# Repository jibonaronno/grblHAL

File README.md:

# grblHAL
STM32F401 GRBL Controller over BlackPill board.

Schematic and layout are completed. Screw Terminal Connectors and optos are aligned. Added 4 TMC2208.<br>

### Inspired from <a href="https://github.com/avizienis/Minimal-Black-Pill--STM32F4xx-BOB-for-grblHAL">Minimal-Black-Pill--STM32F4xx-BOB-for-grblHAL</a><br>
<br>

### Our Kicad design below.<br/>
<br>
<br>
<br>

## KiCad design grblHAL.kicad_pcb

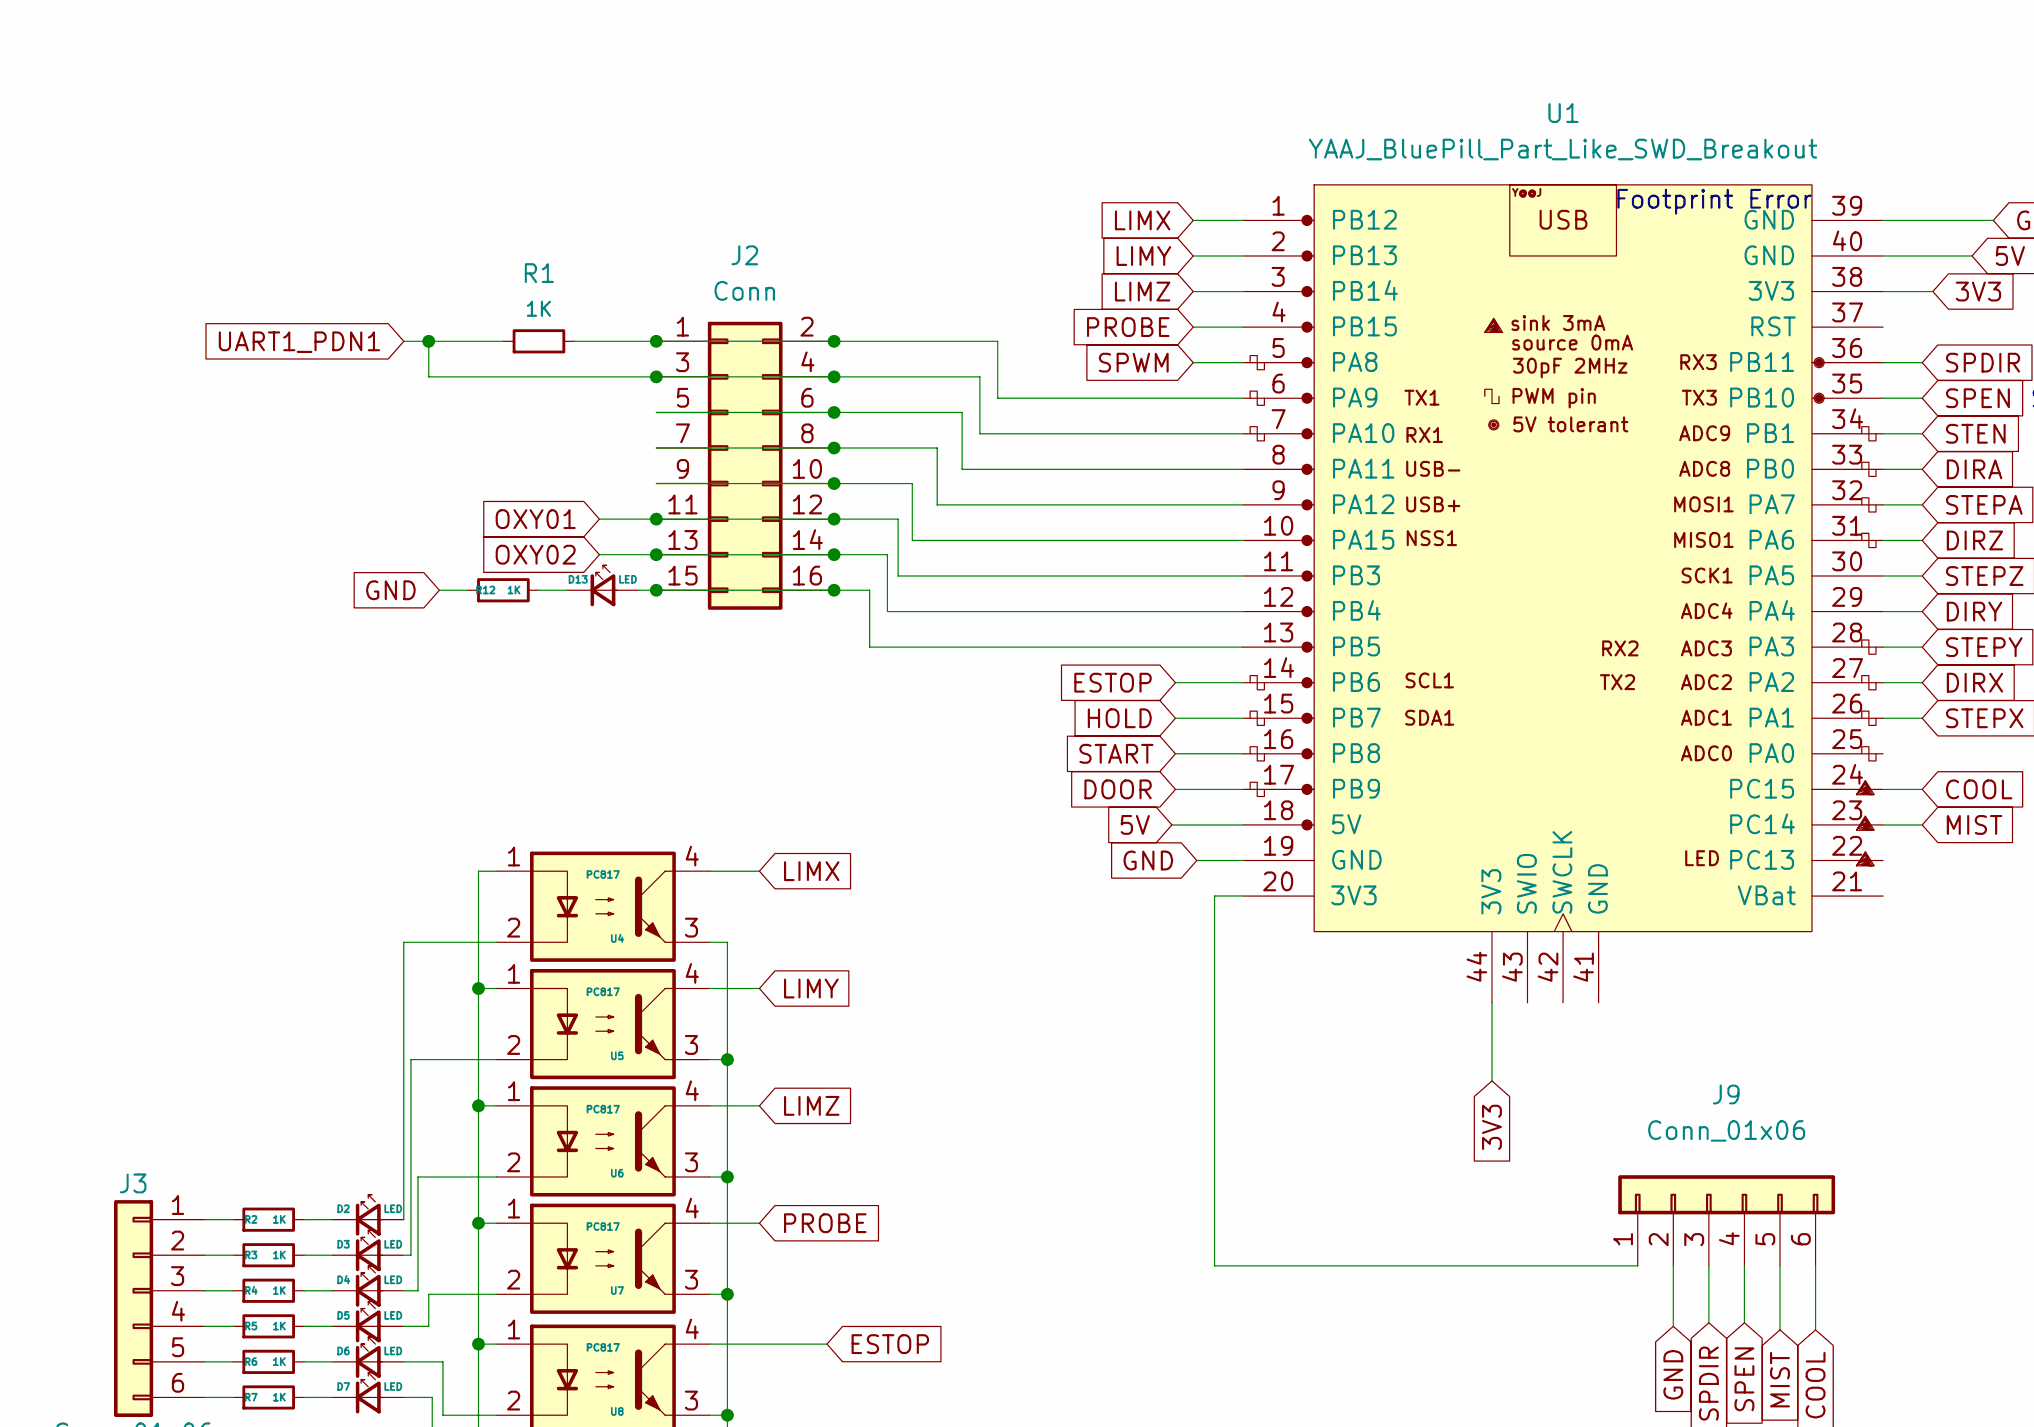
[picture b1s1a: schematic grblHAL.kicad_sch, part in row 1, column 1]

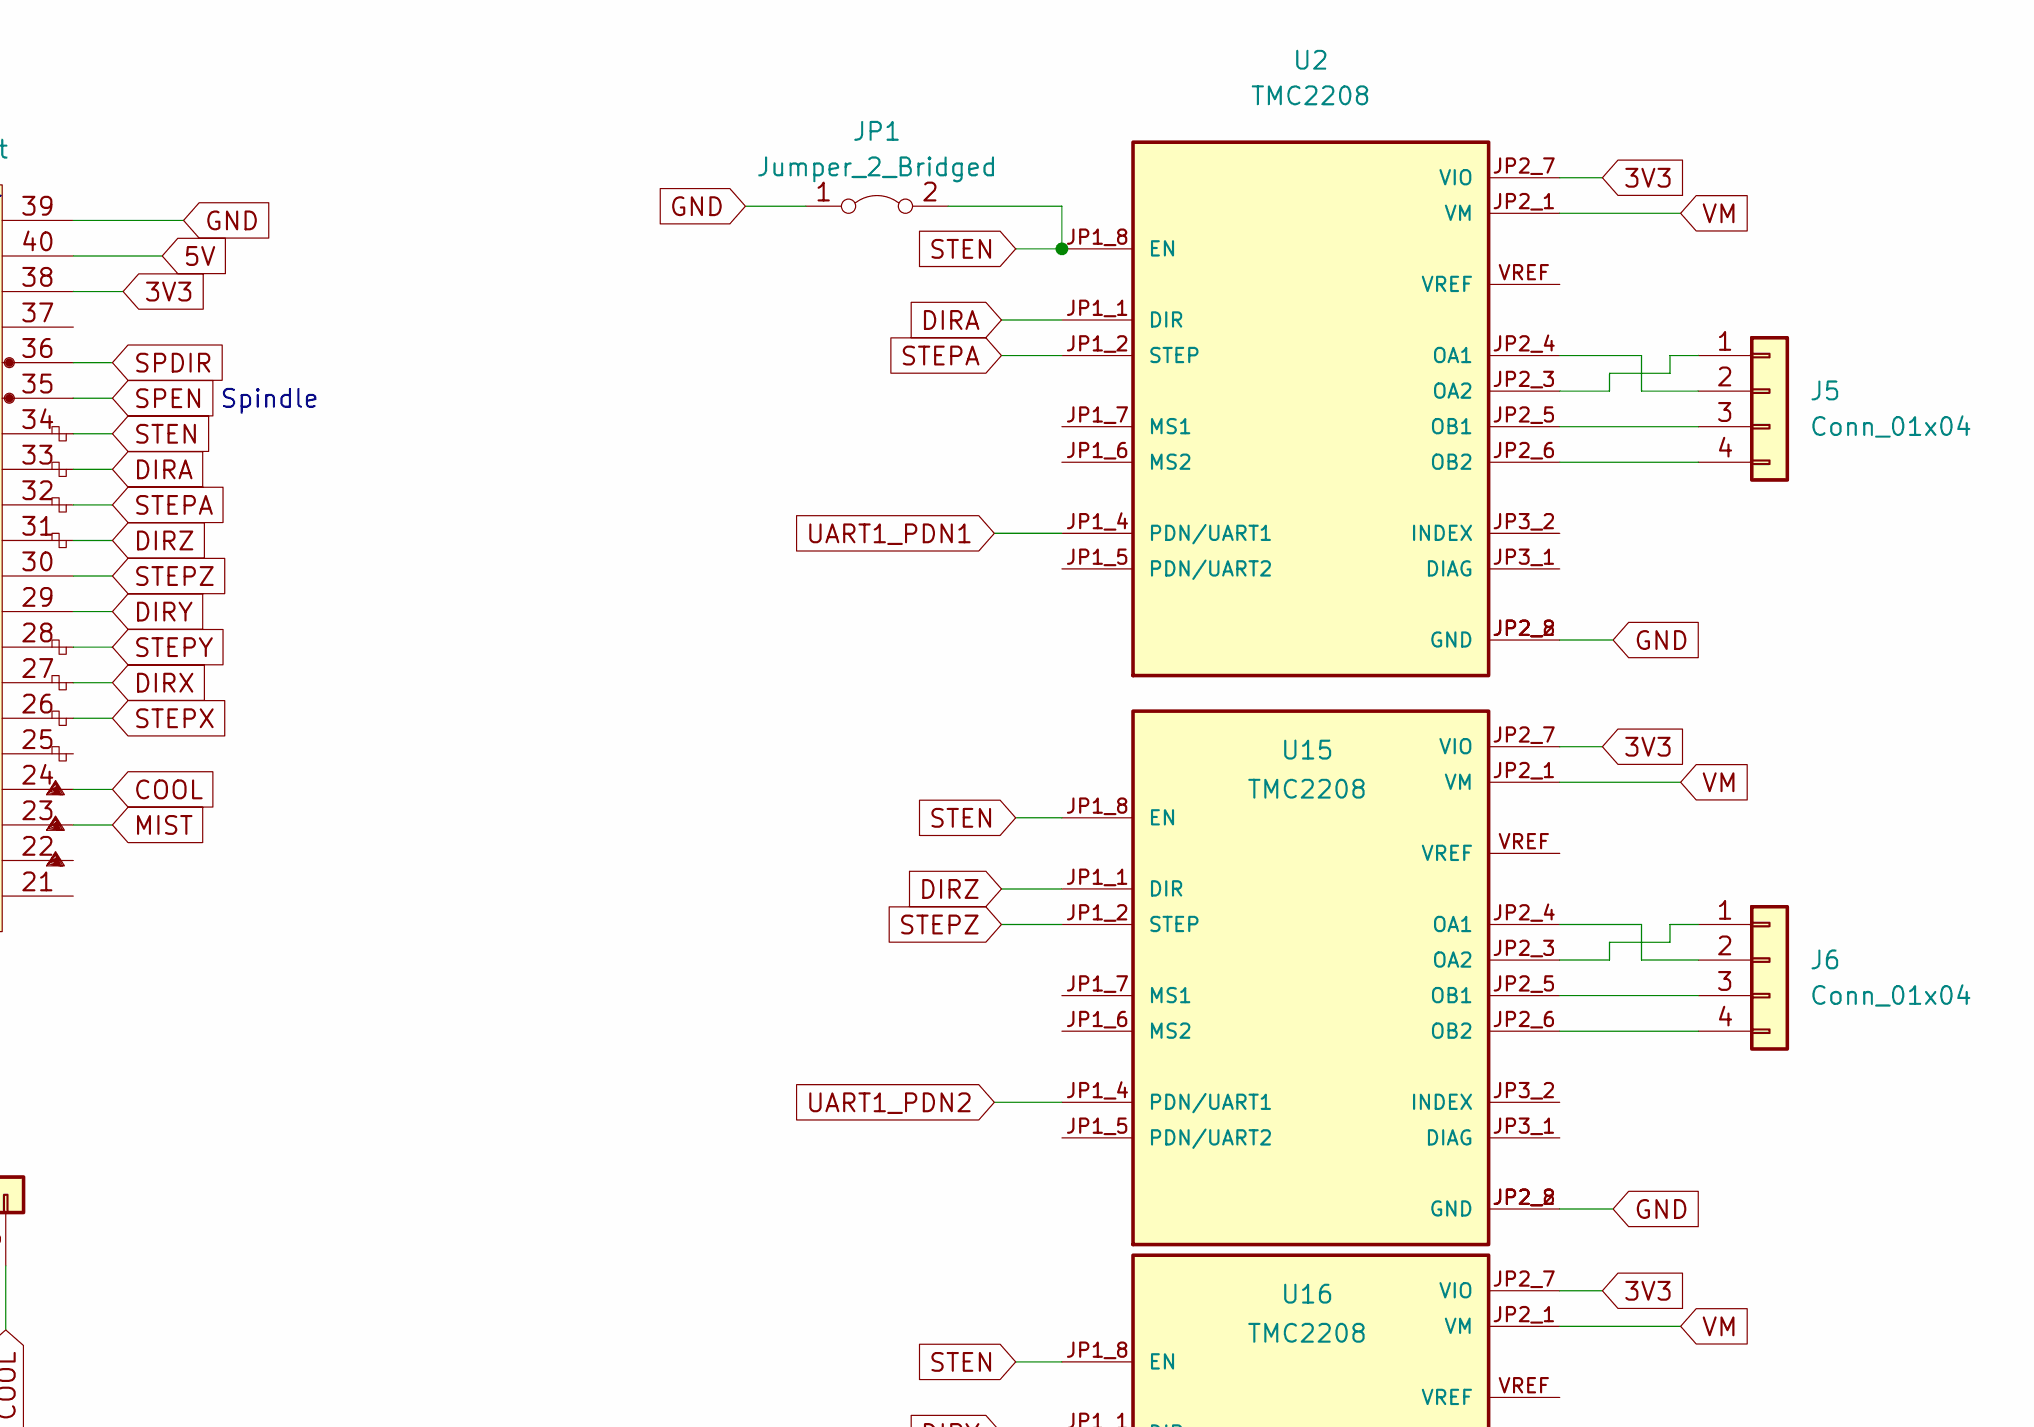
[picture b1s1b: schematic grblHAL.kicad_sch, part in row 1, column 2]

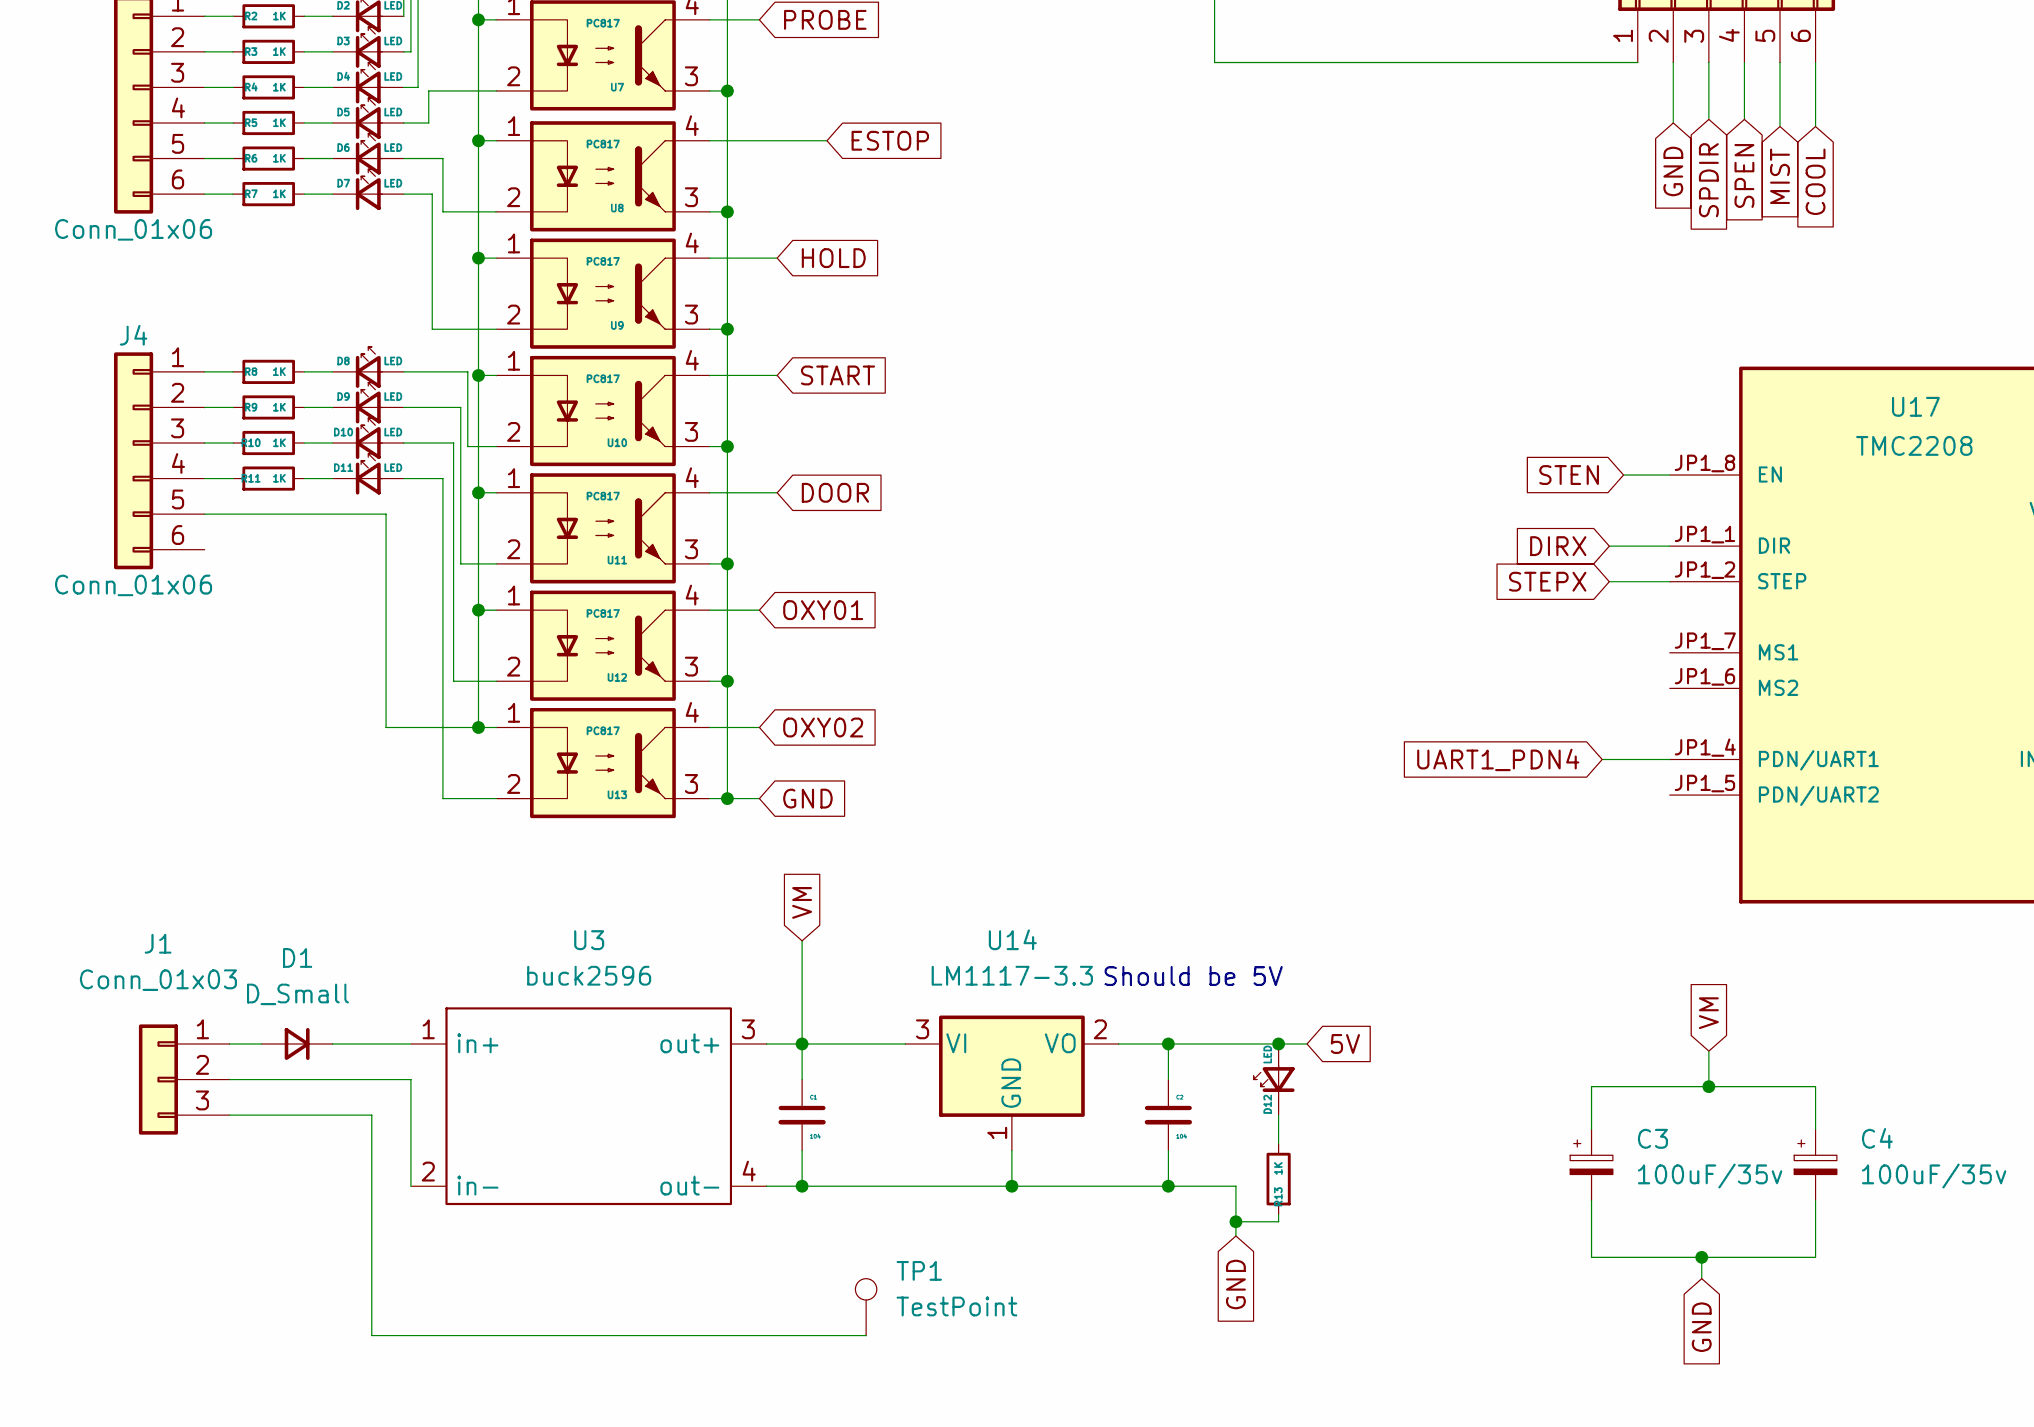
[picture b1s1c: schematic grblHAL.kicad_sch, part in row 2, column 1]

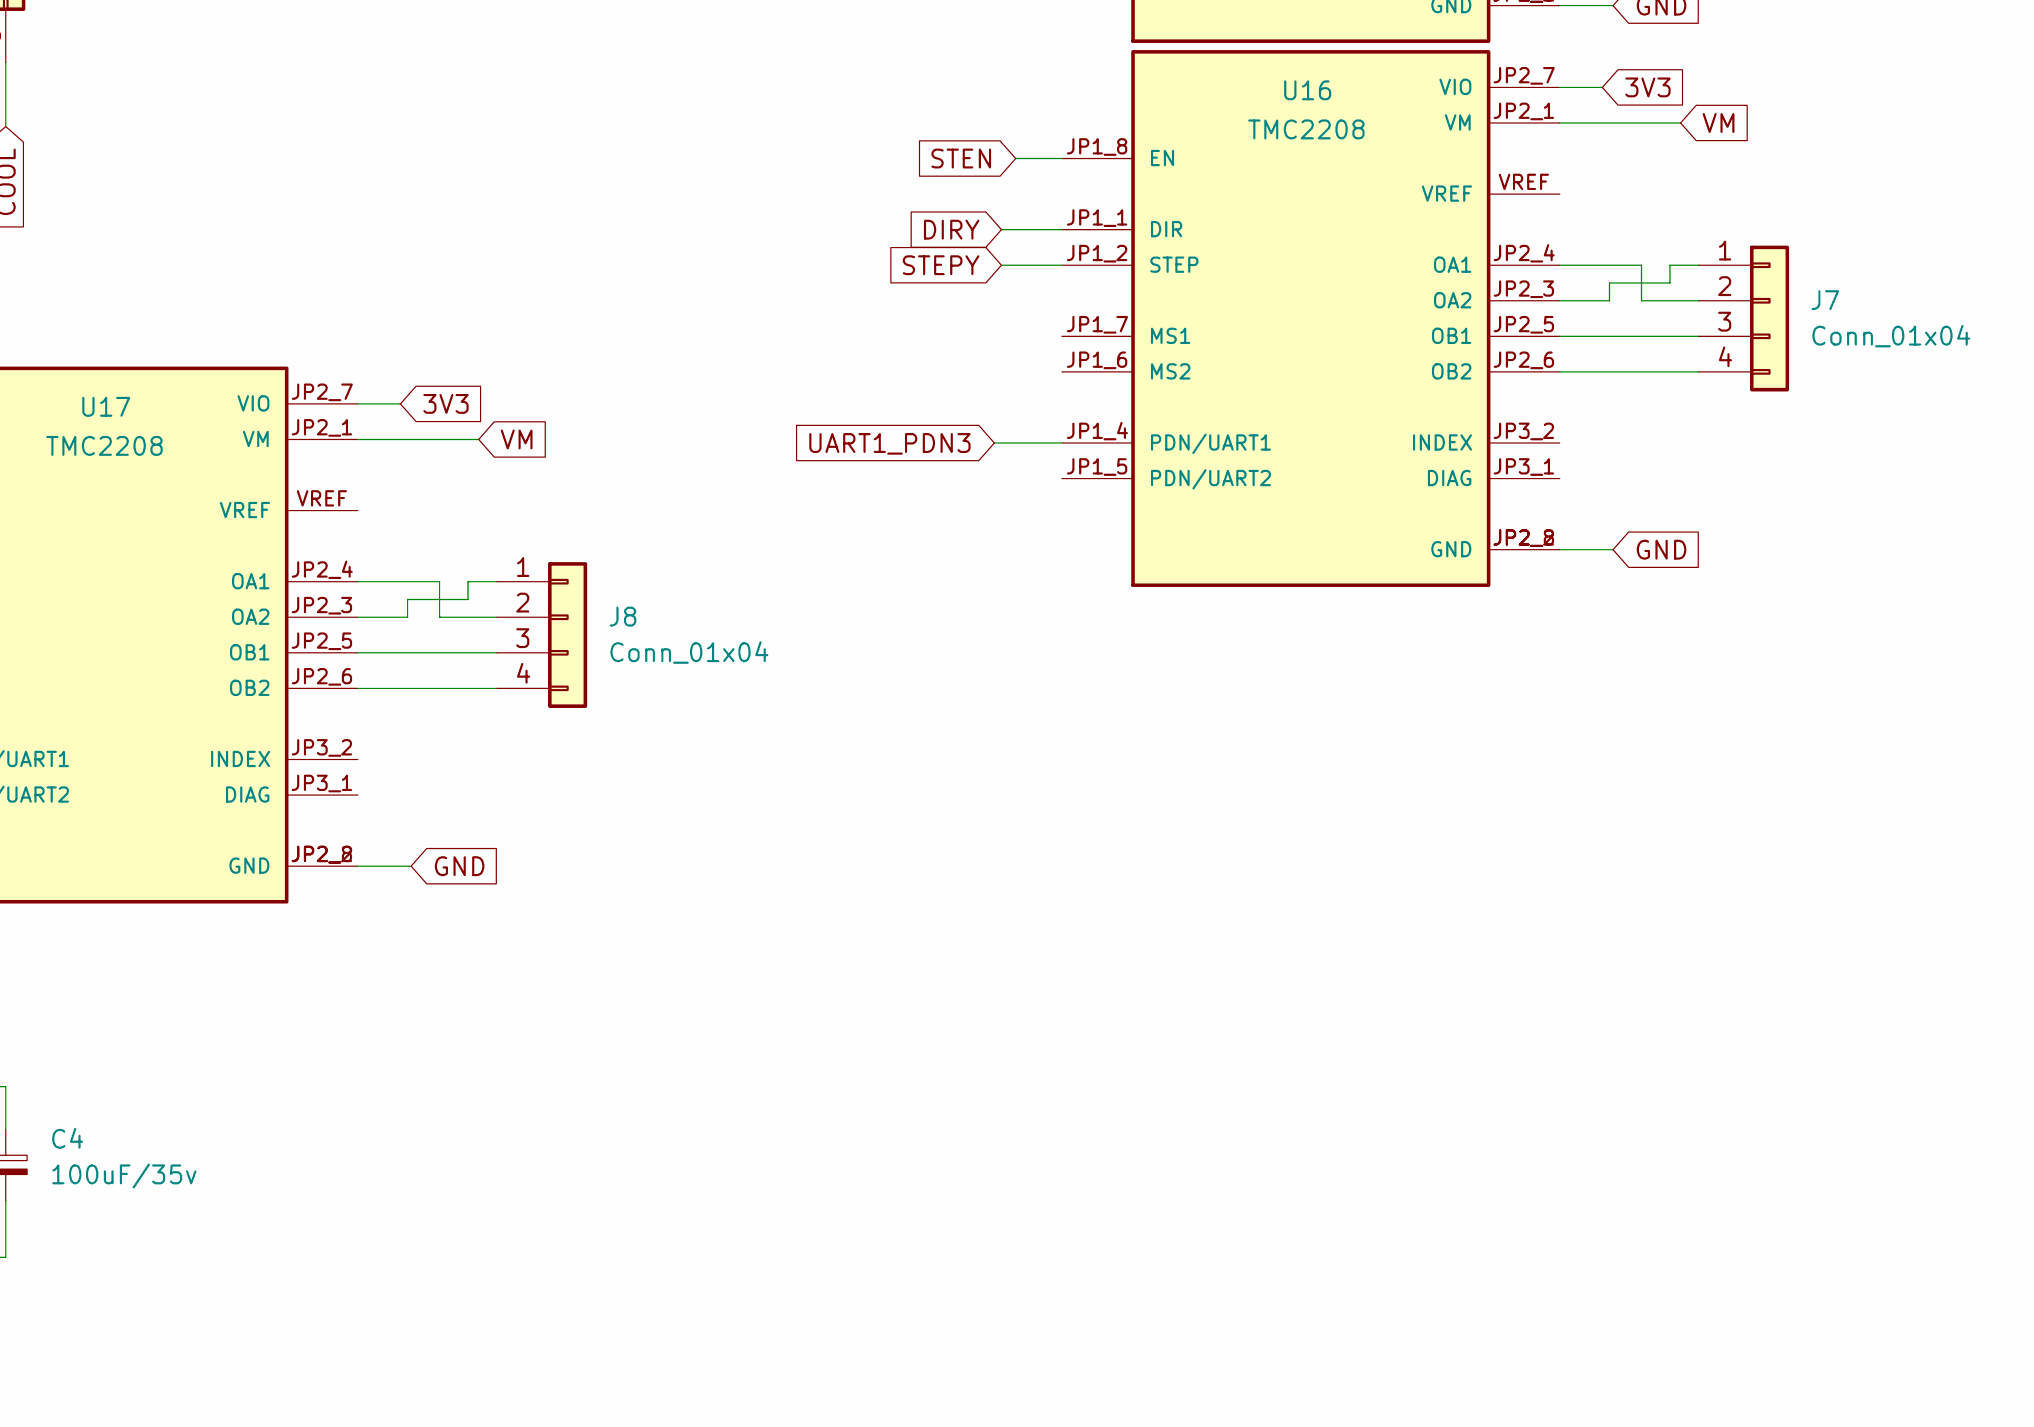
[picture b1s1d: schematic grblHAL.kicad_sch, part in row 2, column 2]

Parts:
C1, C2: 104; C_1206_3216Metric_Pad1.33x1.80mm_HandSolder
C3, C4: 100uF/35v; CP_Radial_D8.0mm_P3.50mm
D1: D_Small; D_SMA
D2, D3, D4, D5, D6, D7, D8, D9, D10, D11, D12, D13: LED; LED_1206_3216Metric_Pad1.42x1.75mm_HandSolder
J1: Conn_01x03; PhoenixContact_MSTBA_2,5_3-G_1x03_P5.00mm_Horizontal
J2: Conn; PinHeader_2x08_P2.54mm_Vertical
J3, J4: Conn_01x06; PhoenixContact_MSTBA_2,5_6-G-5,08_1x06_P5.08mm_Horizontal
J5, J6, J7, J8: Conn_01x04; PinHeader_1x04_P2.54mm_Vertical
J9: Conn_01x06; PinHeader_1x06_P2.54mm_Vertical
JP1: Jumper_2_Bridged; TestPoint_2Pads_Pitch2.54mm_Drill0.8mm
R1, R2, R3, R4, R5, R6, R7, R8, R9, R10, R11, R12, R13: 1K; R_1206_3216Metric_Pad1.30x1.75mm_HandSolder
TP1: TestPoint; PinSocket_1x01_P2.54mm_Vertical
U1: YAAJ_BluePill_Part_Like_SWD_Breakout; YAAJ_BluePill_SWD_1
U2, U15, U16, U17: TMC2208; MODULE_TMC2208_SILENTSTEPSTICK
U3: buck2596; DC_DC_LM2596_small
U4, U5, U6, U7, U8, U9, U10, U11, U12, U13: PC817; DIP-4_W7.62mm
U14: LM1117-3.3; SOT-223-3_TabPin2

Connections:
3V3: U1.38 (3V3), U1.44 (3V3), U2.JP2_7 (VIO), U15.JP2_7 (VIO), U16.JP2_7 (VIO), U17.JP2_7 (VIO)
5V: C2.1, D12.2 (A), U1.18 (5V), U1.40 (GND), U14.2 (VO)
COOL: J9.6, U1.24 (PC15)
DIRA: U1.33 (PB0), U2.JP1_1 (DIR)
DIRX: U1.27 (PA2), U17.JP1_1 (DIR)
DIRY: U1.29 (PA4), U16.JP1_1 (DIR)
DIRZ: U1.31 (PA6), U15.JP1_1 (DIR)
DOOR: U1.17 (PB9), U11.4
ESTOP: U1.14 (PB6), U8.4
GND: C1.2, C2.2, C3.2, C4.2, J9.2, JP1.1 (A), R12.1, R13.1, U1.19 (GND), U1.39 (GND), U2.JP2_2 (GND), U2.JP2_8 (GND), U3.4 (out-), U4.3, U5.3, U6.3, U7.3, U8.3, U9.3, U10.3, U11.3, U12.3, U13.3, U14.1 (GND), U15.JP2_2 (GND), U15.JP2_8 (GND), U16.JP2_2 (GND), U16.JP2_8 (GND), U17.JP2_2 (GND), U17.JP2_8 (GND)
HOLD: U1.15 (PB7), U9.4
LIMX: U1.1 (PB12), U4.4
LIMY: U1.2 (PB13), U5.4
LIMZ: U1.3 (PB14), U6.4
MIST: J9.5, U1.23 (PC14)
unnamed: D1.1 (K), U3.1 (in+)
unnamed: D1.2 (A), J1.1
unnamed: D2.1 (K), R2.2
unnamed: D2.2 (A), U4.2
unnamed: D3.1 (K), R3.2
unnamed: D3.2 (A), U5.2
unnamed: D4.1 (K), R4.2
unnamed: D4.2 (A), U6.2
unnamed: D5.1 (K), R5.2
unnamed: D5.2 (A), U7.2
unnamed: D6.1 (K), R6.2
unnamed: D6.2 (A), U8.2
unnamed: D7.1 (K), R7.2
unnamed: D7.2 (A), U9.2
unnamed: D8.1 (K), R8.2
unnamed: D8.2 (A), U10.2
unnamed: D9.1 (K), R9.2
unnamed: D9.2 (A), U11.2
unnamed: D10.1 (K), R10.2
unnamed: D10.2 (A), U12.2
unnamed: D11.1 (K), R11.2
unnamed: D11.2 (A), U13.2
unnamed: D12.1 (K), R13.2
unnamed: D13.1 (K), R12.2
unnamed: D13.2 (A), J2.15, J2.16, U1.13 (PB5)
unnamed: J1.2, U3.2 (in-)
unnamed: J1.3, TP1.1
unnamed: J2.1, J2.2, R1.2, U1.6 (PA9)
unnamed: J2.5, J2.6, U1.8 (PA11)
unnamed: J2.7, J2.8, U1.9 (PA12)
unnamed: J2.9, J2.10, U1.10 (PA15)
unnamed: J3.1, R2.1
unnamed: J3.2, R3.1
unnamed: J3.3, R4.1
unnamed: J3.4, R5.1
unnamed: J3.5, R6.1
unnamed: J3.6, R7.1
unnamed: J4.1, R8.1
unnamed: J4.2, R9.1
unnamed: J4.3, R10.1
unnamed: J4.4, R11.1
unnamed: J4.5, U4.1, U5.1, U6.1, U7.1, U8.1, U9.1, U10.1, U11.1, U12.1, U13.1
unnamed: J5.1, U2.JP2_3 (OA2)
unnamed: J5.2, U2.JP2_4 (OA1)
unnamed: J5.3, U2.JP2_5 (OB1)
unnamed: J5.4, U2.JP2_6 (OB2)
unnamed: J6.1, U15.JP2_3 (OA2)
unnamed: J6.2, U15.JP2_4 (OA1)
unnamed: J6.3, U15.JP2_5 (OB1)
unnamed: J6.4, U15.JP2_6 (OB2)
unnamed: J7.1, U16.JP2_3 (OA2)
unnamed: J7.2, U16.JP2_4 (OA1)
unnamed: J7.3, U16.JP2_5 (OB1)
unnamed: J7.4, U16.JP2_6 (OB2)
unnamed: J8.1, U17.JP2_3 (OA2)
unnamed: J8.2, U17.JP2_4 (OA1)
unnamed: J8.3, U17.JP2_5 (OB1)
unnamed: J8.4, U17.JP2_6 (OB2)
unnamed: J9.1, U1.20 (3V3)
OXY01: J2.11, J2.12, U1.11 (PB3), U12.4
OXY02: J2.13, J2.14, U1.12 (PB4), U13.4
PROBE: U1.4 (PB15), U7.4
SPDIR: J9.3, U1.36 (PB11)
SPEN: J9.4, U1.35 (PB10)
SPWM: U1.5 (PA8)
START: U1.16 (PB8), U10.4
STEN: JP1.2 (B), U1.34 (PB1), U2.JP1_8 (EN), U15.JP1_8 (EN), U16.JP1_8 (EN), U17.JP1_8 (EN)
STEPA: U1.32 (PA7), U2.JP1_2 (STEP)
STEPX: U1.26 (PA1), U17.JP1_2 (STEP)
STEPY: U1.28 (PA3), U16.JP1_2 (STEP)
STEPZ: U1.30 (PA5), U15.JP1_2 (STEP)
UART1_PDN1: J2.3, J2.4, R1.1, U1.7 (PA10), U2.JP1_4 (PDN/UART1)
UART1_PDN2: U15.JP1_4 (PDN/UART1)
UART1_PDN3: U16.JP1_4 (PDN/UART1)
UART1_PDN4: U17.JP1_4 (PDN/UART1)
VM: C1.1, C3.1, C4.1, U2.JP2_1 (VM), U3.3 (out+), U14.3 (VI), U15.JP2_1 (VM), U16.JP2_1 (VM), U17.JP2_1 (VM)

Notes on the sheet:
Spindle
Footprint Error
Should be 5V

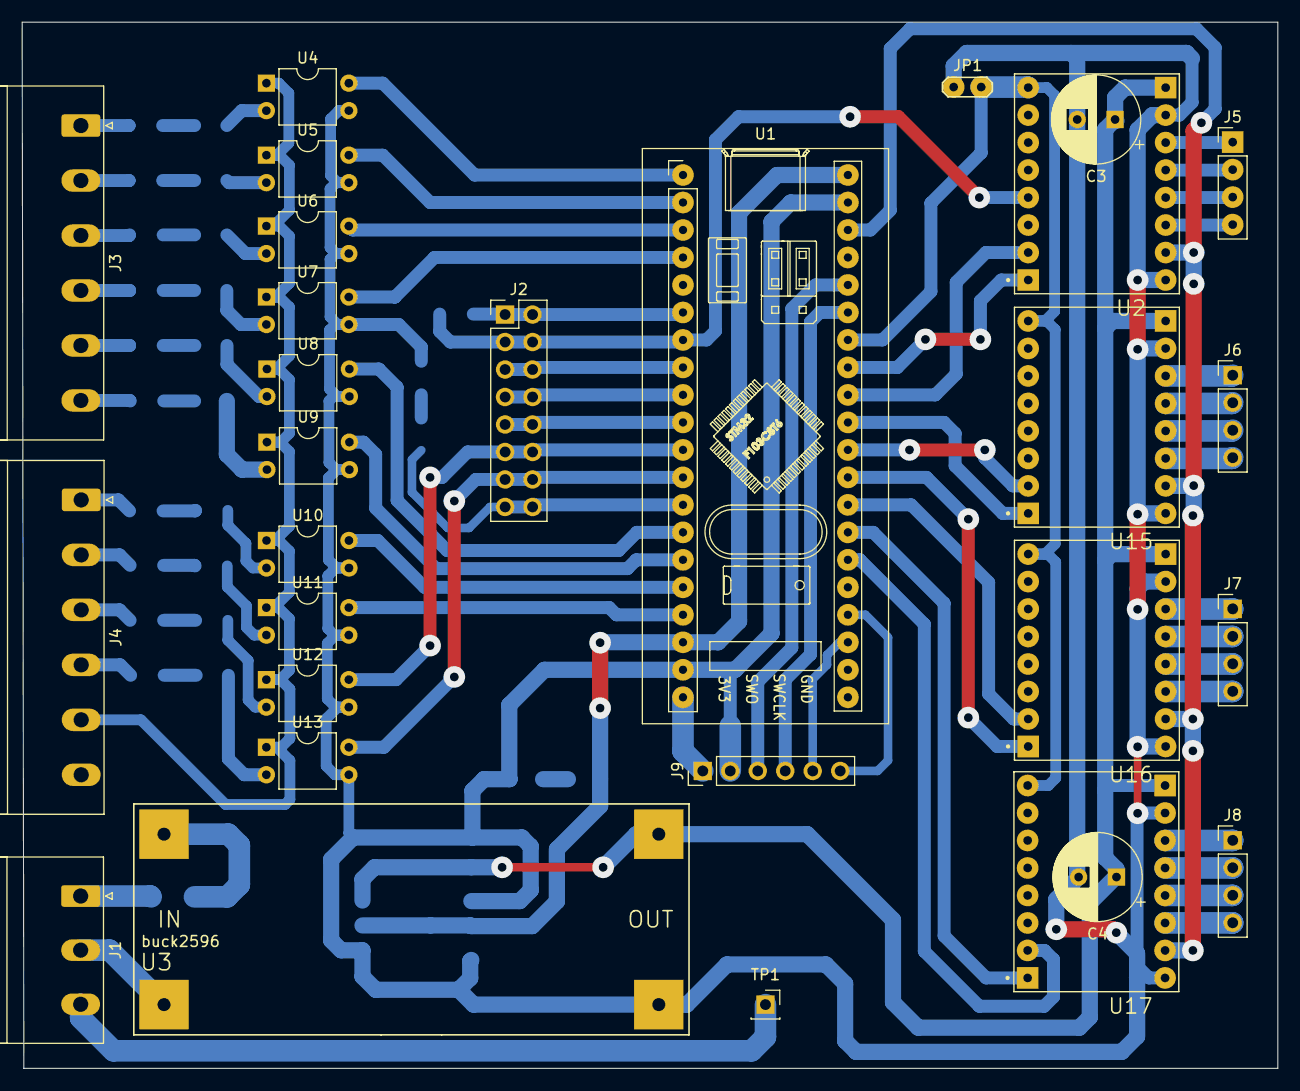
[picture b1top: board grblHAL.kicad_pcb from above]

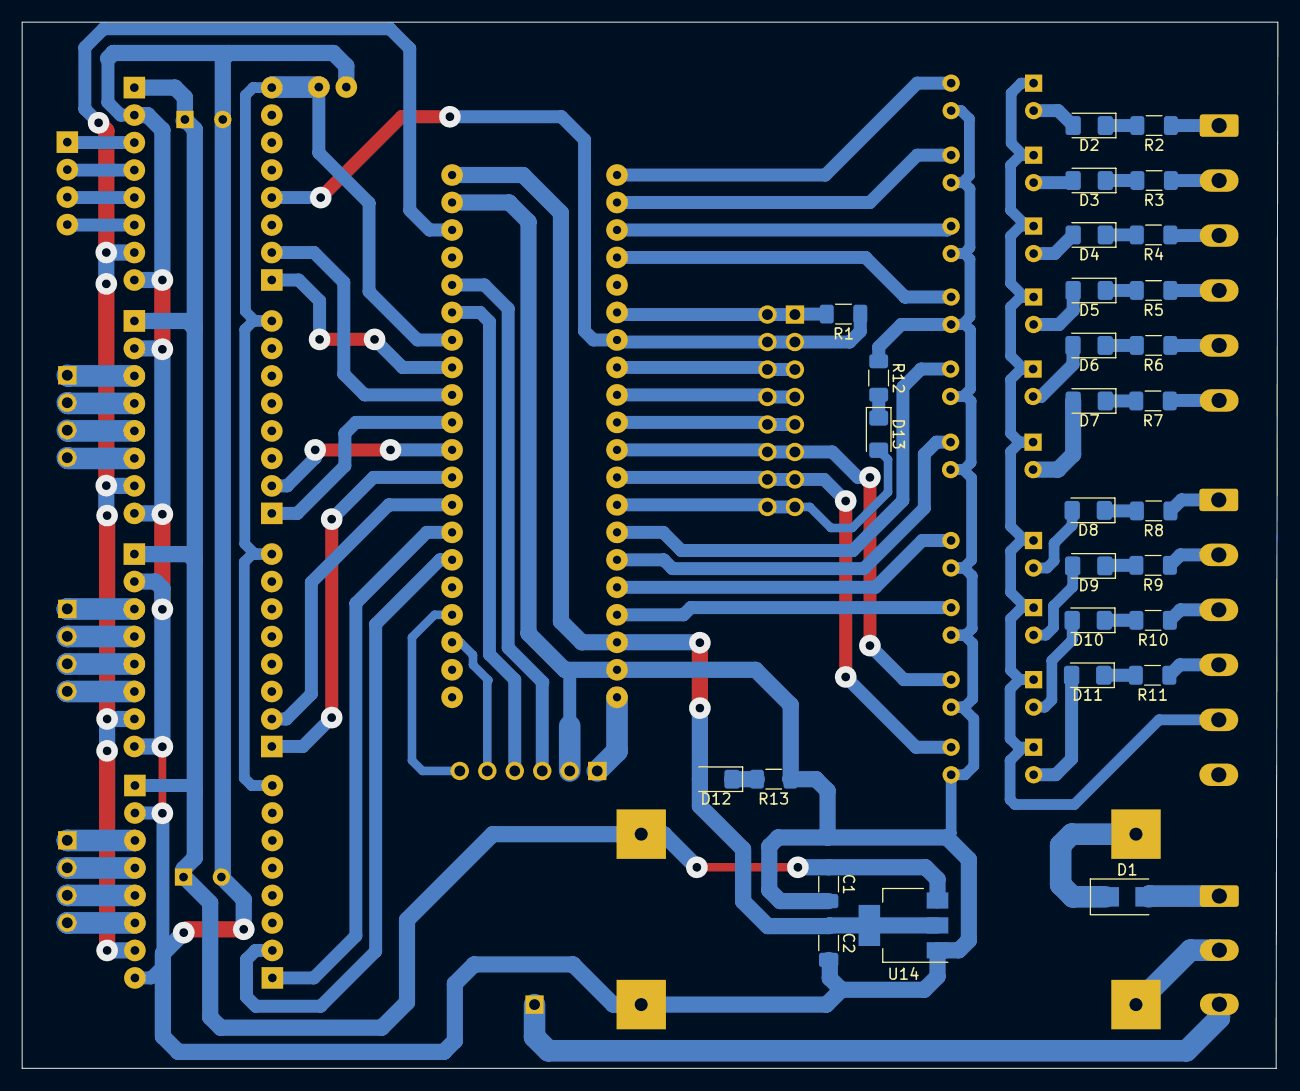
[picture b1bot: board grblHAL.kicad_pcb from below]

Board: 2 copper layers, 116.0 x 96.7 mm, 58 parts (29 on the bottom side), 87 nets.

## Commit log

2023-01-15 Nets Opto 1 TMC
2023-01-15 Schematic Layout Nets Opto 1 TMC Stage 1
2023-01-15 Schematic Layout Nets Opto 4 TMC Stage 2
2023-01-15 Schematic Full Layout Nets Opto Connector 4-TMC Stage 3
